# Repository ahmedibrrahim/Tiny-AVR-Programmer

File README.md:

# Tiny-AVR-Programmer
Here you get your own very small AVR programmer board that you can put in your keychain.

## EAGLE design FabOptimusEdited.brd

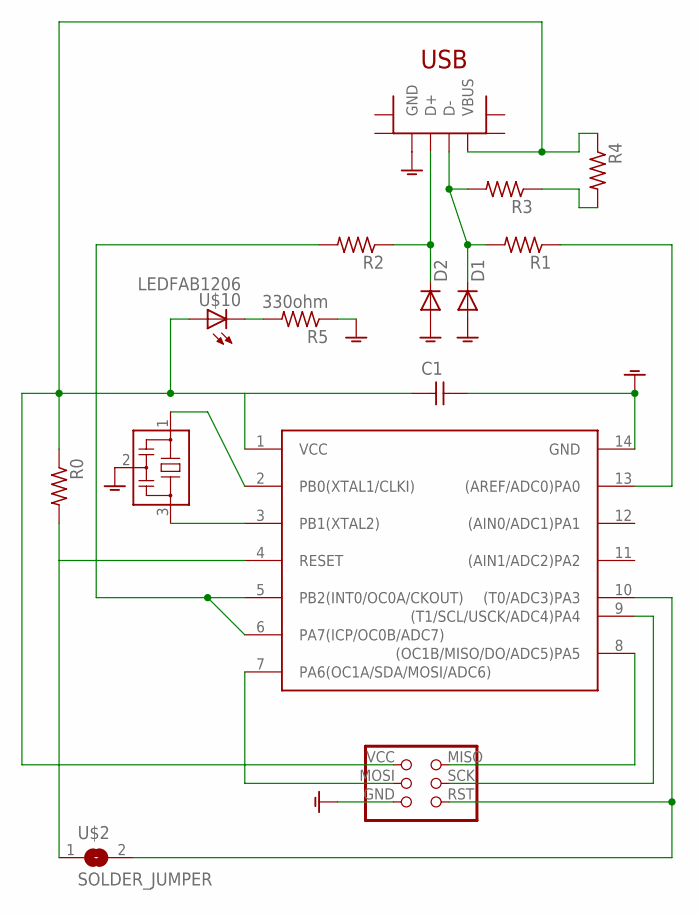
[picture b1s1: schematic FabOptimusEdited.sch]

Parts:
C1: CAP-UNPOLARIZEDFAB; C1206FAB
D1, D2: DIODESOD123; SOD123
IC1: ATTINY44-SSU; SOIC14_ATTTINY44
JP1: 2X3PINHEADER
R0, R1, R2, R3, R4: RES-US1206FAB; R1206FAB
R5: 330ohm; R1206FAB
U$1: RESONATOR; EFOBM
U$2: SOLDER_JUMPER; SOLDERJUMPER
U$8: USB_MINIB
U$10: LEDFAB1206; LED1206FAB

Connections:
GND: C1.2, D1.ANODE (A), D2.ANODE (A), IC1.14 (GND), JP1.GND (1), R5.1, U$1.2, U$8.GND
unnamed: IC1.2 (PB0(XTAL1/CLKI)), U$1.1
unnamed: D2.CATHODE (C), R2.1, U$8.D+
unnamed: IC1.9 ((T1/SCL/USCK/ADC4)PA4), JP1.SCK (4)
unnamed: D1.CATHODE (C), R1.2, R3.2, U$8.D-
unnamed: IC1.7 (PA6(OC1A/SDA/MOSI/ADC6)), JP1.MOSI (3)
unnamed: IC1.5 (PB2(INT0/OC0A/CKOUT)), IC1.6 (PA7(ICP/OC0B/ADC7)), R2.2
unnamed: IC1.3 (PB1(XTAL2)), U$1.3
unnamed: IC1.13 ((AREF/ADC0)PA0), R1.1
unnamed: IC1.8 ((OC1B/MISO/DO/ADC5)PA5), JP1.MISO (6)
unnamed: IC1.10 ((T0/ADC3)PA3), JP1.RST (2), U$2.2
unnamed: IC1.4 (RESET), R0.2, U$2.1
unnamed: R3.1, R4.2
unnamed: R5.2, U$10.2 (C)
R4: C1.1, IC1.1 (VCC), JP1.VCC (5), R0.1, R4.1, U$8.V (VBUS), U$10.1 (A)

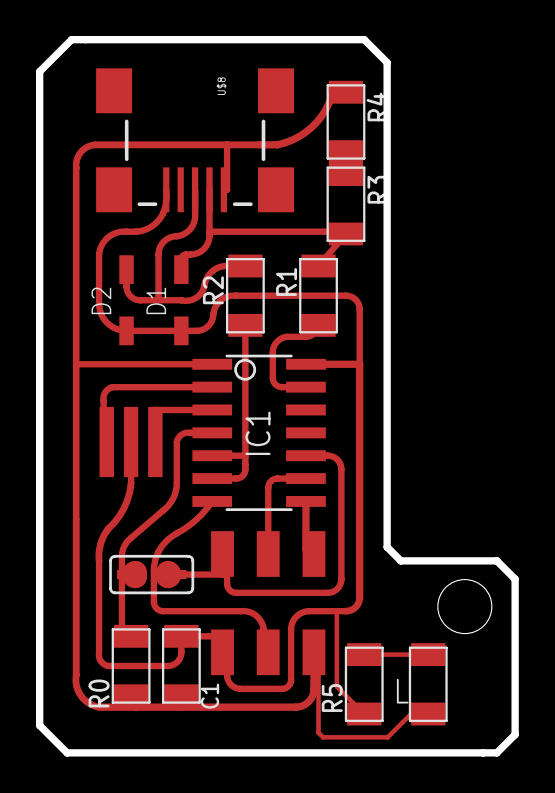
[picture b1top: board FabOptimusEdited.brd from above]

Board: 2 copper layers, 26.4 x 39.6 mm, 15 parts (0 on the bottom side), 15 nets.

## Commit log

2021-03-15 Uploading source files
